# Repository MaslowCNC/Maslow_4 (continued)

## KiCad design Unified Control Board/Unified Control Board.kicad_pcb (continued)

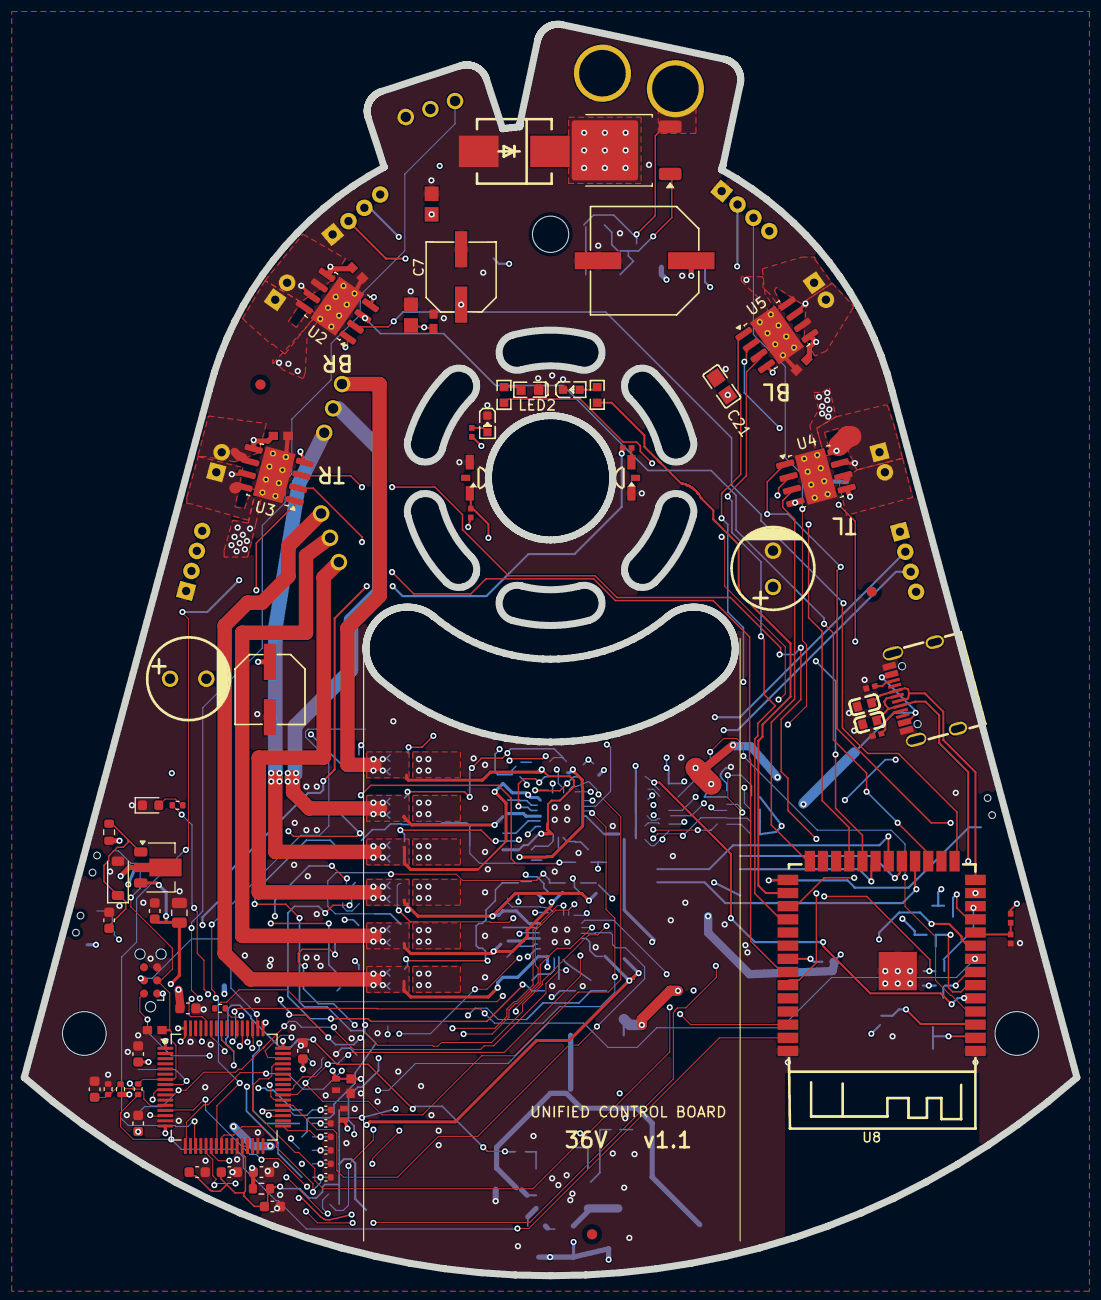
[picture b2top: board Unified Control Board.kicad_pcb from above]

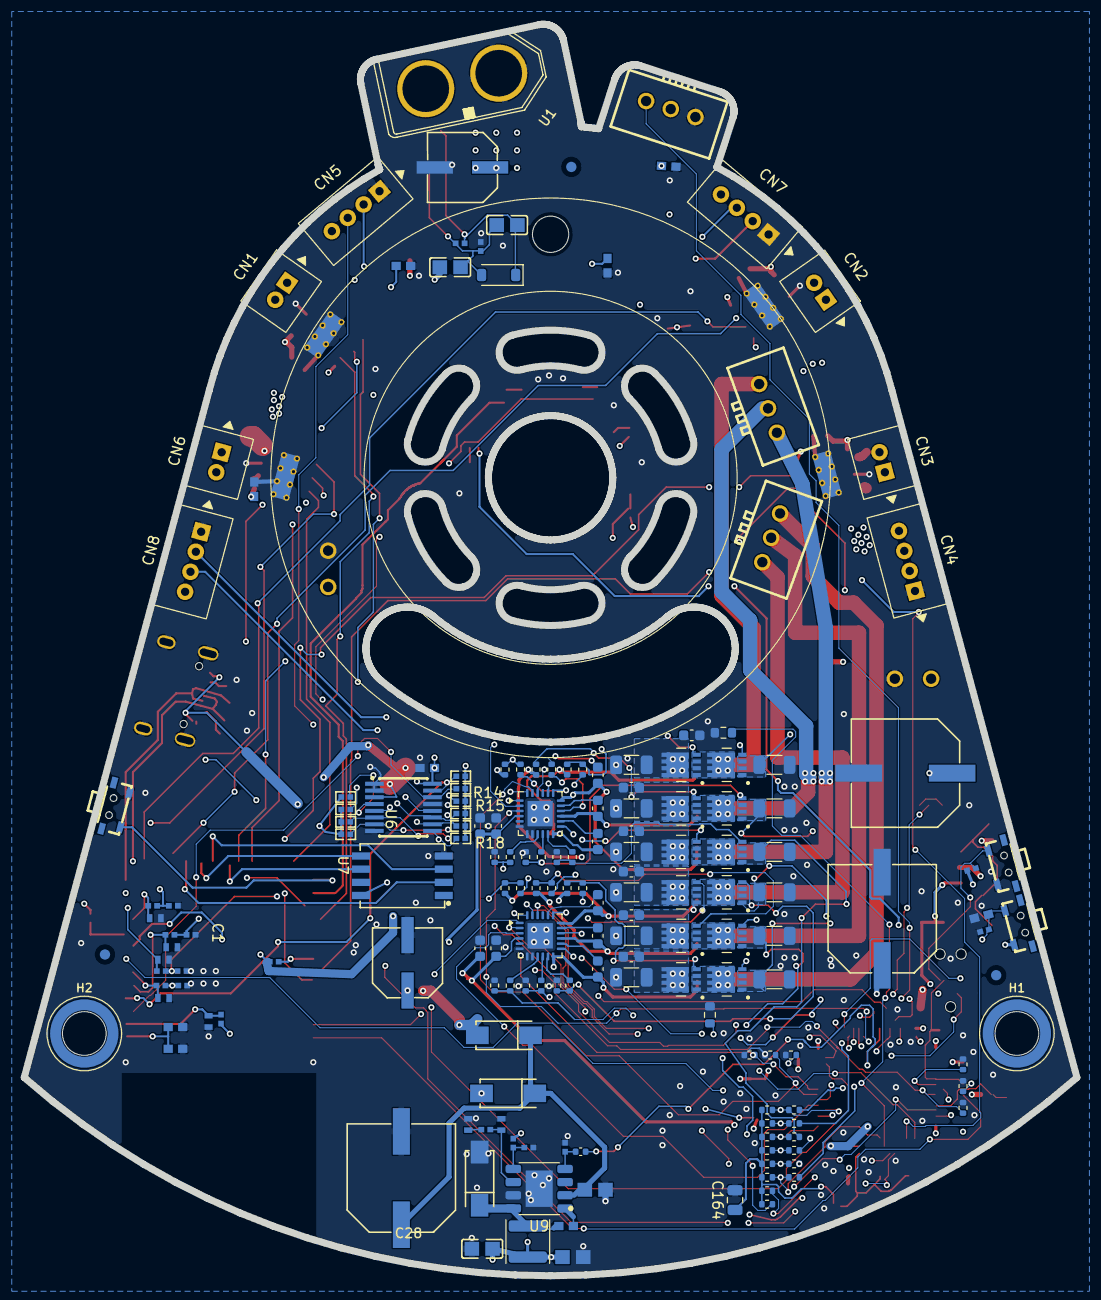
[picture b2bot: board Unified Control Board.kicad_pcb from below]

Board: 4 copper layers, 101.6 x 120.8 mm, 245 parts (172 on the bottom side), 145 nets.

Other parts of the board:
FID1, FID2, FID3, FID4, FID5, FID6: Fiducial; Fiducial_1mm_Mask2mm

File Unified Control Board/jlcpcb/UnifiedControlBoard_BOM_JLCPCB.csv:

"Comment","Designator","Footprint","LCSC Part #","Quantity"
"22uF","C1,C7,C10,C18","CAP-SMD_BD6.3-L6.6-W6.6-LS7.3-FD","C267472","4"
"100nF/100V","C5,C9,C16,C112,C113,C114,C132,C133,C134,C160,C161,C162,C163","C0603","C15725","13"
"1uF","C8,C11,C19,C20,C26,C40,C44","C0402","C52923","7"
"22uF","C21,C33,C56,C63,C164","C0805","C45783","5"
"100nF/50V","C22,C31,C34,C36,C42,C49,C54,C61,C101,C102,C103,C105,C121,C122,C123,C125,C140,C141,C142,C143,C146,C147,C150,C152,C153","C_0603_1608Metric","C14663","25"
"10uF/25V","C23,C72,C151","C0805","C15850","3"
"22pF","C24,C25","C0603","C105620","2"
"330uF/50V","C27,C74,C75","CAP-SMD_BD10.0-L10.3-W10.3-LS10.9-FD","C178596","3"
"220uF/50V","C28","CAP-SMD_BD10.0-L10.3-W10.3-LS10.9-FD","C116211","1"
"12nF","C29","C0402","C576739","1"
"82pF","C30","C0402","C107011","1"
"10uF","C32","C0805","C440198","1"
"100uF/50V","C39,C60","CAP-TH_BD8.0-P3.50-D0.6-FD","C88728","2"
"220nF/100V","C73","C0805","C513710","1"
"10uF/25V","C104,C124","C_0603_1608Metric","C91606","2"
"100pF","C106,C107,C108,C126,C127,C128","C_0402_1005Metric","C1546","6"
"1uF/100V","C109,C110,C111,C129,C130,C131","C_1206_3216Metric","C13832","6"
"4.7uF","C144","C_0603_1608Metric","C19666","1"
"1uF/50V","C145","C_0603_1608Metric","C15849","1"
"10pF","C165","C_0402_1005Metric","C32949","1"
"IR12-21C/TR8","CGQ1","LED-SMD_IR12-21C-TR8","C53672","1"
"B02B-PASK(LF)(SN)","CN1,CN2,CN3,CN6","CONN-TH_B02B-PASK","C158050","4"
"B04B-PASK(LF)(SN)","CN4,CN5,CN7,CN8","CONN-TH_B04B-PASK","C265078","4"
"B3B-XH-2(LF)(SN)","CN9,CN10,CN11","CONN-TH_B3B-XH-2-LF-SN","C158003","3"
"RB050L-60TE25","D1,D2,D5","SMA_L4.2-W2.6-LS5.3-RD","C209642","3"
"SMCJ36A","D3","SMC_L7.1-W6.2-LS8.1-R-RD","C151282","1"
"BZT52C15","D6","D_SOD-123","C173427","1"
"BZT52C13","D10","D_SOD-123","C173428","1"
"SMTSOM330BTR","H1,H2","SMTSO-M3_SMD-Ring_Hole4.22","C5221843","2"
"PT12-21C/TR8","IR1","SENSOR-SMD_L3.0-W2.0-RD","C53674","1"
"4.7uH","L1","L_APV_ANR4030","C167874","1"
"LED-0603_R","LED1","LED0603_RED","C2286","1"
"FC-DA1608BK-470H10","LED2","LED0603-RD","C84266","1"
"green","LED3,LED4","LED0603-RD-YELLOW","C2289","2"
"ME50P06-G","Q1","TO-252-2","C165230","1"
"AON7264E","Q10,Q11,Q12,Q13,Q14,Q15,Q20,Q21,Q22,Q23,Q24,Q25","AOS_DFN-8-1EP_3x3mm_P0.65mm","C431191","12"
"BCX56-16","Q30","SOT-89-3","C123402","1"
"680Ω","R1,R11,R12,R21","R0402","C25130","4"
"120Ω","R2,R3","R0603","C22787","2"
"2.2kΩ","R4","R0402","C25879","1"
"1kΩ","R5,R7,R14,R15,R16,R17,R18,R22,R23,R24,R116,R117,R118,R146,R147,R148,R175,R176,R177","R0402","C11702","19"
"5.1kΩ","R8,R13","R0402","C25905","2"
"10kΩ","R9,R10,R19,R20,R25,R26,R28,R38,R39,R45,R107,R108,R109,R110,R111,R112,R137,R138,R139,R140,R141,R142,R173,R174","R_0402_1005Metric","C25744","24"
"62kΩ","R27","R0402","C37825","1"
"20kΩ","R29","R0402","C25765","1"
"200kΩ","R30","R0402","C25764","1"
"7.5kΩ","R31","R0402","C25918","1"
"100Ω","R44","R0402","C25076","1"
"330Ω","R58","R0402","C25104","1"
"47kΩ","R59","R0402","C25792","1"
"100kΩ","R60,R171","R0402","C25741","2"
"15","R101,R102,R103,R104,R105,R106,R131,R132,R133,R134,R135,R136","R_0402_1005Metric","C25083","12"
"5m","R113,R114,R115,R143,R144,R145","R_1206_3216Metric","C201272","6"
"31.6k","R119,R120,R121,R149,R150,R151","R_0402_1005Metric","C11463","6"
"4.7k","R160,R161,R162,R163,R164,R165","R_0402_1005Metric","C25900","6"
"10k","R170","R_0603_1608Metric","C25804","1"
"6.8k","R172","R_0402_1005Metric","C25917","1"
"4.7","R178","R_0603_1608Metric","C144651","1"
"10k NTC","RT1,RT2","R_0603_1608Metric","C13564","2"
"TSA002A3512A02","SW1,SW2,SW3","SW-SMD_BZCN_TSA002A35XXX","C2888932","3"
"XT60PB-M.G.Y","U1","CONN-TH_XT60PB-M","C19268037","1"
"DRV8251ADDAR","U2,U3,U4,U5","SOIC-8-1EP_DDA0008B_ThermalVias_0.3mm","C5218844","4"
"TCA9546A","U6","SOP-16_L5.0-W4.4-P0.65-LS6.4-BL","C201653","1"
"ZDSD01GLGEAG","U7","LGA-8_L6.0-W8.0-P1.27-BL","C2830323","1"
"ESP32-S3-WROOM-1","U8","ESP32-S3-WROOM-1","C2913204","1"
"TPS54360BDDAR","U9","AP64350SP_SO-8-EP","C524806","1"
"STM32G474RBT3","U20","LQFP-64_10x10mm_P0.5mm","C1235414","1"
"DRV8300DRGE","U21,U22","VQFN-24-1EP_4x4mm_P0.5mm_EP2.45x2.45mm","C3655801","2"
"KH-TYPE-C-16P","USB1","USB-C-SMD_KH-TYPE-C-16P","C709357","1"

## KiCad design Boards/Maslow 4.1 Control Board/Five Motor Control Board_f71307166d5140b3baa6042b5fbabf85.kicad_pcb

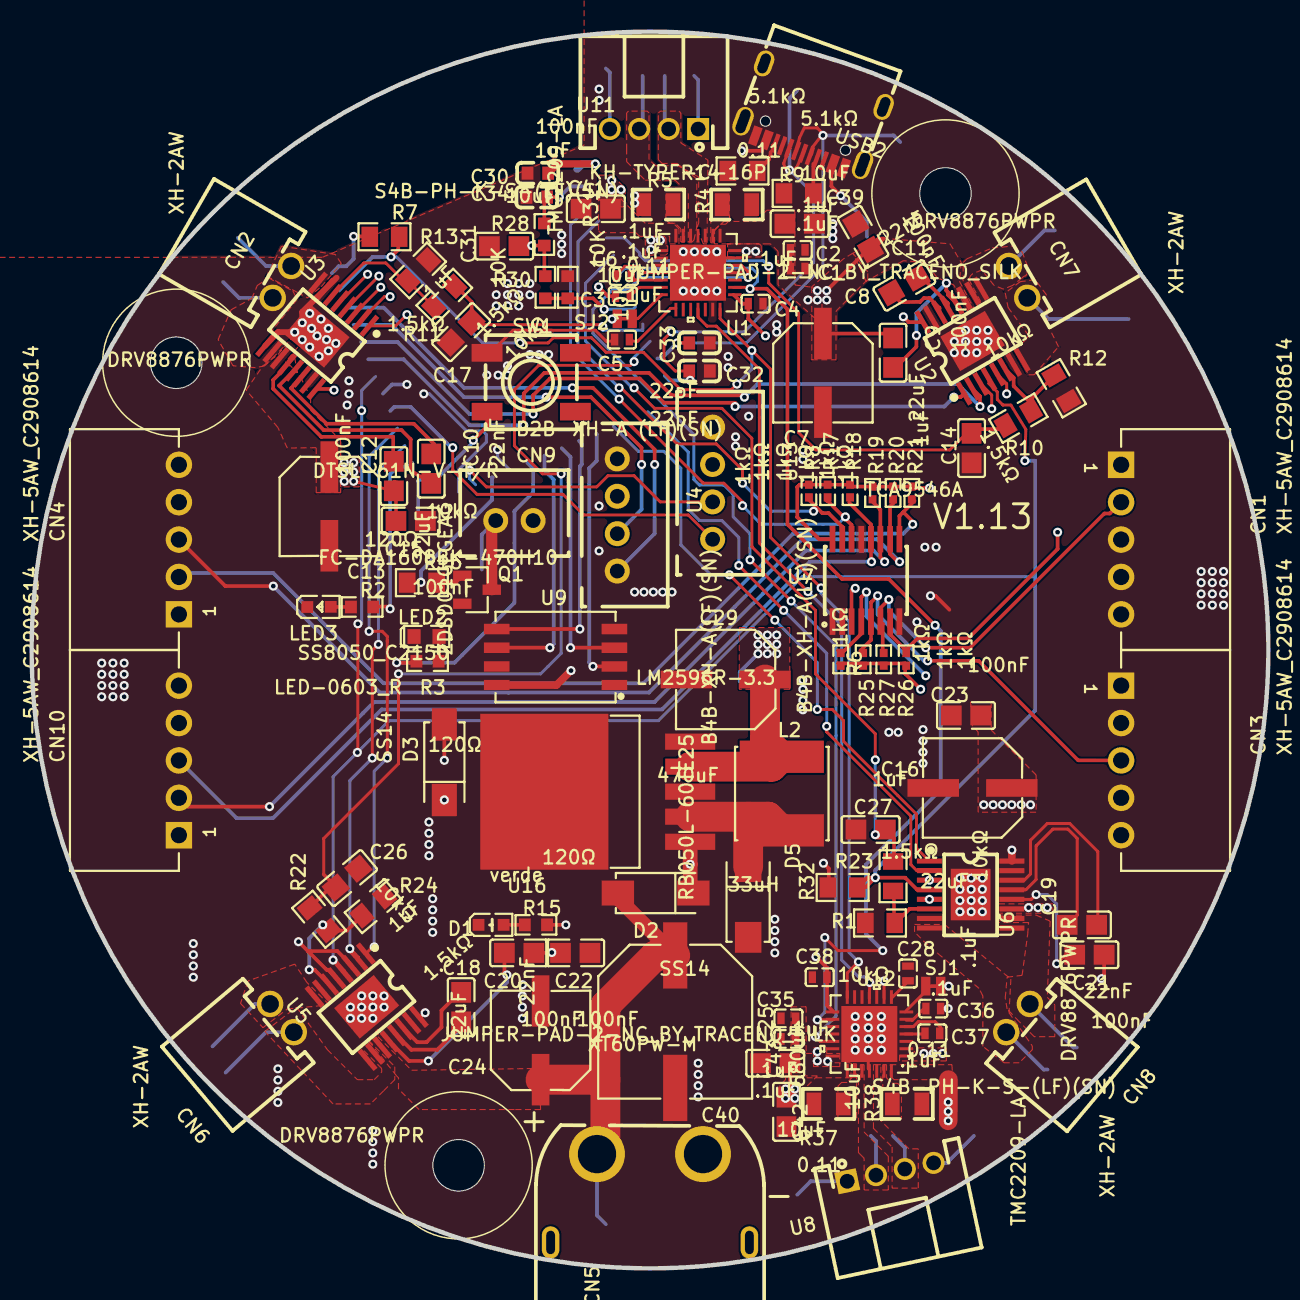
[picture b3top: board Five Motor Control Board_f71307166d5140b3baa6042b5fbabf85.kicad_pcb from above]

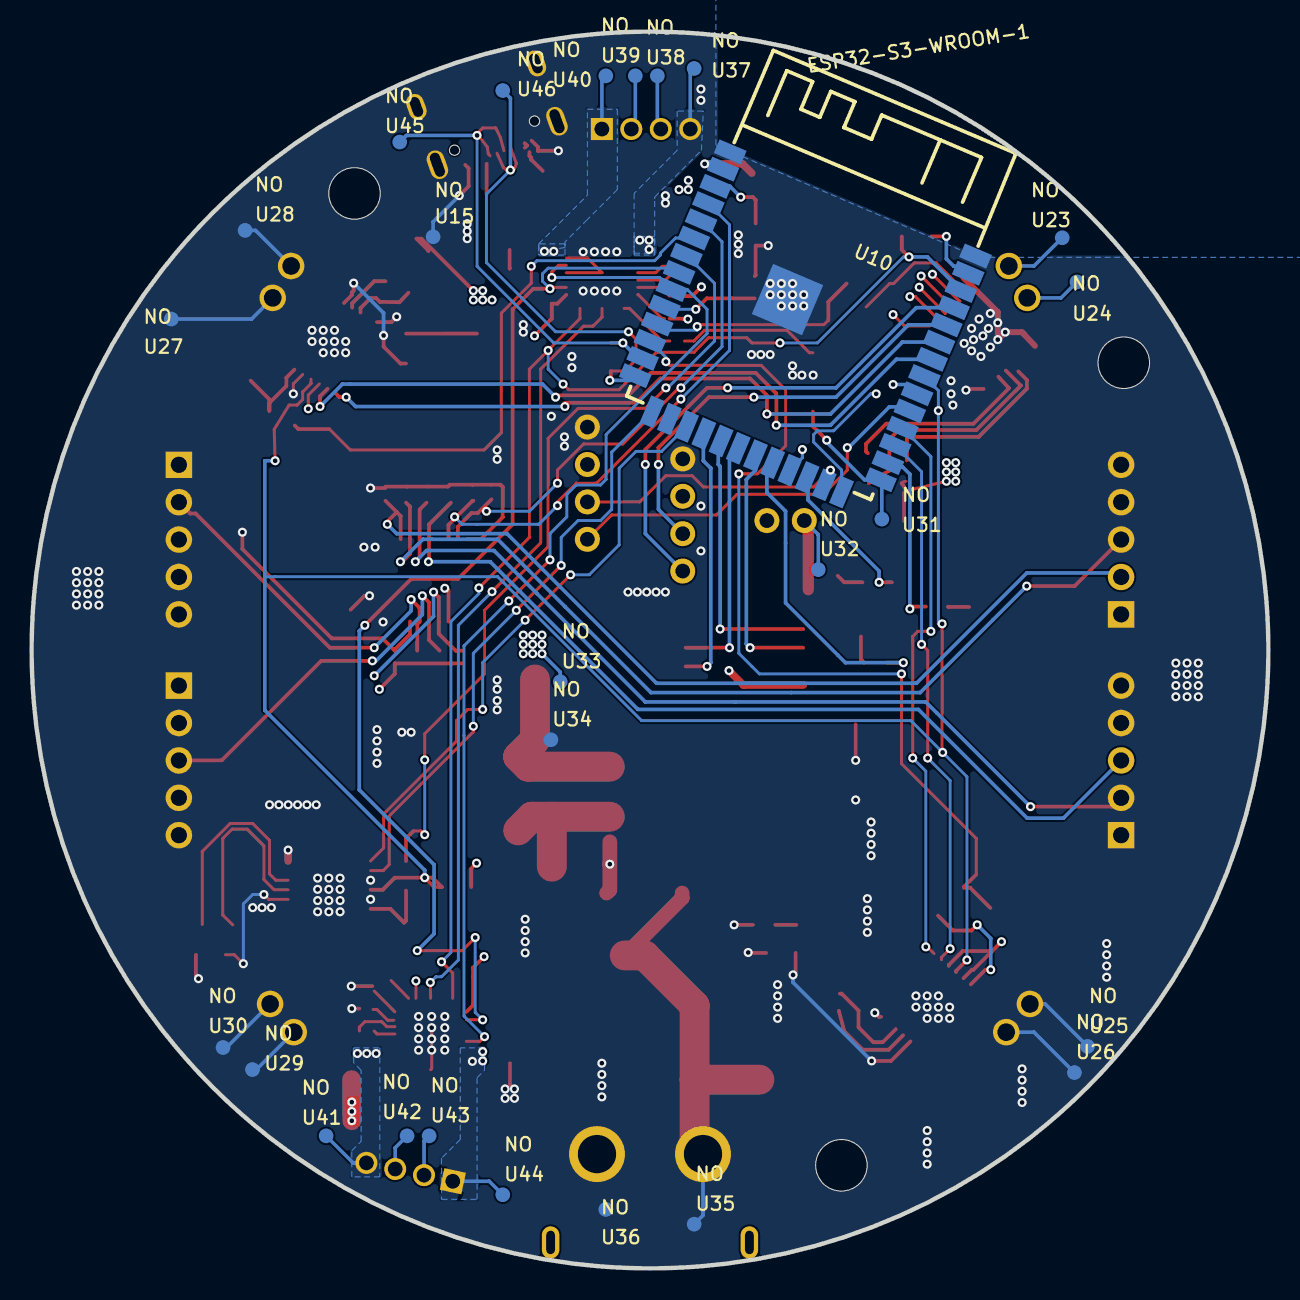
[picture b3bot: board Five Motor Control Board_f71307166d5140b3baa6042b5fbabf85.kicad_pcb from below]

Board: 4 copper layers, 84.0 x 84.0 mm, 140 parts (26 on the bottom side), 103 nets.

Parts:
C1, C2, C3, C4, C5, C6, C25, C28, C35, C36, C37, C38: .1uF; C0402
C7, C13, C16, C24: 22uF; CAP-SMD_BD6.3-L6.6-W6.6-LS7.3-FD
C8, C10, C18, C19: 22nF; C0805
C9, C11, C12, C15, C20, C21, C22, C23: 100nF; C0805
C14, C17, C26, C27: 1uF; C0805
C29: 470uF; CAP-SMD_BD6.3-L6.6-W6.6-LS7.6-RD
C30: 100nF; C0603
C31, C39, C41, C42, C43: 10uF; C0805
C32, C33: 22pF; C0603
C34: 1uF; C0603
C40: 680uF; CAP-SMD_BD10.0-L10.3-W10.3-LS10.9-FD
CN1, CN3, CN4, CN10: XH-5AW_C2908614; CONN-TH_5P-P2.54_XH-5AW_C2908614
CN2, CN6, CN7, CN8: XH-2AW; CONN-TH_2P-P2.50_XH-2AW
CN5: XT60PW-M; CONN-TH_XT60PW-M
CN9: B2B-XH-A (LF)(SN); CONN-TH_B2B-XH-A-LF-SN
D1: verde; LED0603-R-RD
D2, D3: SS14; SMA_L4.2-W2.6-LS5.3-RD
D5: RB050L-60TE25; SMA_L4.3-W2.7-LS5.1-RD
Hole_gge29897: Hole_gge29897
Hole_gge29907: Hole_gge29907
Hole_gge29912: Hole_gge29912
L2: 33uH; IND-SMD_L6.0-W6.0
LED2: LED-0603_R; LED0603_RED
LED3: FC-DA1608BK-470H10; LED0603-RD
Q1: SS8050_C2150; SOT-23-3_L2.9-W1.3-P1.90-LS2.4-BR
R1, R7, R12, R13, R24: 1.5kΩ; R0805
R2, R3, R15: 120Ω; R0603
R4, R5, R37, R38: 0.11; R0805
R6, R8, R17, R18, R19, R20, R21, R25, R26, R27: 1kΩ; R0402
R9, R14: 5.1kΩ; R0805
R10, R11, R16, R22, R23, R32: 10kΩ; R0805
R28, R30, R31: 10K; R0603
SJ1, SJ2: JUMPER-PAD-2-NC_BY_TRACENO_SILK; PAD-JUMPER-2-NC_BY_TRACE_NO_SILK
SW1: DTSL-61N-V-T/R; SW-SMD_4P-L6.2-W6.4-P4.00-LS7.2
U1, U12: TMC2209-LA
U2, U3, U5, U6: DRV8876PWPR; HTSSOP-16_L5.0-W4.4-P0.65-LS6.4-BL-EP
U4, U13: B4B-XH-A(LF)(SN); CONN-TH_B4B-XH-A-LF-SN
U7: TCA9546A; SOP-16_L5.0-W4.4-P0.65-LS6.4-BL
U8, U11: S4B-PH-K-S-(LF)(SN); CONN-TH_4P-P2.00_S4B-PH-K-S-LF-SN
U9: ZDSD01GLGEAG; LGA-8_L6.0-W8.0-P1.27-BL
U10: ESP32-S3-WROOM-1
U15, U23, U24, U25, U26, U27, U28, U29, U30, U31, U32, U33, U34, U35, U36, U37, U38, U39, U40, U41, U42, U43, U44, U45, U46: NO; 1-POINT_TEST-POINT
U16: LM2596R-3.3; TO-263-5_L10.2-W8.6-P1.70-LS14.4-TL
USB2: KH-TYPE-C-16P; USB-C-SMD_KH-TYPE-C-16P

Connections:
3V3: C4.1, C29.1, C30.2, C31.2, C38.1, CN1.1, CN3.1, CN4.1, CN10.1, L2.2, R6.2, R8.2, R15.2, R17.2, R18.2, R19.2, R20.2, R21.2, R25.2, R26.1, R27.2, R28.2, R30.2, R32.2, SJ1.1, SJ2.1, U1.15, U2.3, U2.5, U2.16, U3.3, U3.5, U3.16, U4.2, U5.3, U5.5, U5.16, U6.3, U6.5, U6.16, U7.3, U7.16, U9.8, U10.2, U12.9, U12.15, U13.2, U16.4, U33.1
A1+: U8.2, U12.24, U43.1
A1-: U8.1, U12.21, U44.1
A2+: U1.24, U11.2, U39.1
A2-: U1.21, U11.1, U40.1
ADCBL: C26.2, R22.1, U10.12
ADCBR: C27.2, R23.1, U10.7
ADCTL: C17.2, R11.1, U10.11
ADCTR: C14.2, R10.1, U10.6
AUX1: U10.25, U13.3
AUX2: U10.31, U13.4
AXISHEALTHLED: R3.2, U10.22
B1+: U8.3, U12.26, U42.1
B1-: U8.4, U12.1, U41.1
B2+: U1.26, U11.3, U38.1
B2-: U1.1, U11.4, U37.1
BLIN1: U5.1, U10.30
BLIN2: U5.2, U10.29
BLOUT1: CN6.2, U5.8, U25.1
BLOUT2: CN6.1, U5.10, U26.1
BOARDVERSION: R30.1, R31.2, U10.10
BOOT: SW1.2, U10.27, U31.1
BRIN1: U6.1, U10.17
BRIN2: U6.2, U10.15
BROUT1: CN8.2, U6.8, U29.1
BROUT2: CN8.1, U6.10, U30.1
C3_2: C3.2, U1.6
CLKV: U9.3, U10.20
COOLINGFAN: R16.1, U10.24
D1_1: D1.1, R15.1
DIAG: U1.11, U12.11
FAULT: R32.1, U2.4, U3.4, U5.4, U6.4, U10.33
GND: C1.2, C2.2, C4.2, C5.1, C7.2, C11.1, C13.2, C14.1, C15.1, C16.2, C17.1, C22.1, C23.1, C24.2, C25.2, C26.1, C27.1, C28.1, C29.2, C30.1, C31.1, C32.1, C33.1, C34.1, C35.2, C38.2, C39.2, C40.2, C41.2, C42.2, C43.2, CN1.4, CN1.5, CN3.4, CN3.5, CN4.4, CN4.5, CN5.1, CN10.4, CN10.5, D1.2, D5.2, LED2.2, LED3.1, Q1.2, R1.1, R4.2, R5.2, R9.1, R12.1, R13.1, R14.1, R24.1, R31.1, R37.2, R38.2, SW1.4, U1.2, U1.3, U1.13, U1.18, U1.20, U1.25, U1.29, U2.7, U2.9, U2.15, U2.17, U3.7, U3.9, U3.15, U3.17, U4.1, U5.7, U5.9, U5.15, U5.17, U6.7, U6.9, U6.15, U6.17, U7.1, U7.2, U7.8, U7.13, U9.4, U10.1, U10.40, U10.41, U12.2, U12.3, U12.13, U12.18, U12.20, U12.25, U12.29, U13.1, U16.3, U16.5, U34.1, U36.1, USB2.1, USB2.2, USB2.3, USB2.4, USB2.A1, USB2.A12, USB2.B1, USB2.B12
L2_1: D5.1, L2.1, U16.2
LED2_1: LED2.1, R3.1
LED3_2: LED3.2, R2.1
MCU_RST: C34.2, R28.1, U10.3
MISOV: U9.6, U10.21
MOSIV: U9.5, U10.19
MZDIRECTION: U1.19, U10.9, U12.19
MZSTEP: U1.16, U10.8, U12.16
Q1_1: Q1.1, R16.2
Q1_3: CN9.2, Q1.3, U32.1
R4_1: R4.1, U1.23
R5_1: R5.1, U1.27
SCL: R17.1, U7.14, U10.4
SCL0: CN3.3, R25.1, U7.5
SCL1: CN1.3, R26.2, U7.7
SCL2: CN4.3, R20.1, U7.10
SCL3: CN10.3, R18.1, U7.12
SDA: R8.1, U7.15, U10.5
SDA0: CN3.2, R6.1, U7.4
SDA1: CN1.2, R27.1, U7.6
SDA2: CN4.2, R21.1, U7.9
SDA3: CN10.2, R19.1, U7.11
SD_CS: U9.2, U10.18
SERIALRX: U4.3, U10.36
SERIALTX: U4.4, U10.37
TLIN1: U3.1, U10.26
TLIN2: U3.2, U10.23
TLOUT1: CN2.2, U3.8, U23.1
TLOUT2: CN2.1, U3.10, U24.1
TRIN1: U2.1, U10.35
TRIN2: U2.2, U10.34
TRINAMICRX: R7.1, U1.14, U10.38, U12.14
TRINAMICTX: R7.2, U10.39
TROUT1: CN7.2, U2.8, U27.1
TROUT2: CN7.1, U2.10, U28.1
U1_4: C6.1, U1.4
U1_5: C6.2, U1.5
U1_7: SJ2.2, U1.7
U1_8: C5.2, U1.8
U2_6: R10.2, R12.2, U2.6
U2_12: C9.2, U2.12
U2_13: C8.2, U2.13
U2_14: C8.1, U2.14
U3_6: R11.2, R13.2, U3.6
U3_12: C12.2, U3.12
U3_13: C10.2, U3.13
U3_14: C10.1, U3.14
U5_6: R22.2, R24.2, U5.6
U5_12: C20.2, U5.12
U5_13: C18.2, U5.13
U5_14: C18.1, U5.14
U6_6: R1.2, R23.2, U6.6
U6_12: C21.2, U6.12
U6_13: C19.2, U6.13
U6_14: C19.1, U6.14
U12_4: C37.1, U12.4
U12_5: C37.2, U12.5
U12_6: C36.2, U12.6
U12_7: SJ1.2, U12.7
U12_8: C28.2, U12.8
U12_23: R37.1, U12.23
U12_27: R38.1, U12.27
U16_1: D2.1, D3.1, U16.1
USB2_A5: R9.2, USB2.A5
USB2_B5: R14.2, USB2.B5
USB5V: D3.2, U15.1, USB2.A4, USB2.A9, USB2.B4, USB2.B9
USBD+: C32.2, U10.14, U46.1, USB2.A6, USB2.B6
USBD-: C33.2, U10.13, U45.1, USB2.A7, USB2.B7
VCC: C1.1, C2.1, C3.1, C7.1, C9.1, C11.2, C12.1, C13.1, C15.2, C16.1, C20.1, C21.1, C22.2, C23.2, C24.1, C25.1, C35.1, C36.1, C39.1, C40.1, C41.1, C42.1, C43.1, CN5.2, CN9.1, D2.2, U1.22, U1.28, U2.11, U3.11, U5.11, U6.11, U12.22, U12.28, U35.1
WIFILED: R2.2, U10.28

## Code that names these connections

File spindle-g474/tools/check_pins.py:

#!/usr/bin/env python3
"""Check the G474 firmware's pin map (src/board.h) against the board's KiCad netlist.

Exports the netlist of "Unified Control Board/Unified Control Board.kicad_sch" with kicad-cli and
checks every MCU pin the firmware uses, plus the parts around it whose values the firmware
assumes (shunts, sense resistors, VBUS divider, NTCs, BoardVersion divider, XY<->G474 wiring).

    python3 spindle-g474/tools/check_pins.py [--kicad-cli PATH]

Exit status 0 = everything matches.
"""
import argparse, os, shutil, subprocess, sys, tempfile
import xml.etree.ElementTree as ET

HERE = os.path.dirname(os.path.abspath(__file__))
SCH = os.path.join(HERE, "..", "..", "Unified Control Board", "Unified Control Board.kicad_sch")

# U20 (STM32G474RBT3, LQFP64) pin -> (pin name, net) the firmware expects.
MCU = {
    "8": ("PC0", "INHA1"), "9": ("PC1", "INHB1"), "10": ("PC2", "INHC1"),
    "45": ("PA11", "INLA1"), "46": ("PA12", "INLB1"), "37": ("PB15", "INLC1"),
    "38": ("PC6", "INHA2"), "39": ("PC7", "INHB2"), "40": ("PC8", "INHC2"),
    "52": ("PC10", "INLA2"), "53": ("PC11", "INLB2"), "54": ("PC12", "INLC2"),
    "13": ("PA1", "ISA1"), "21": ("PA7", "ISB1"), "24": ("PB0", "ISC1"),
    "33": ("PB11", "ISA2"), "36": ("PB14", "ISB2"), "35": ("PB13", "ISC2"),
    "12": ("PA0", "VBUS_SENSE"), "22": ("PC4", "TEMP1"), "23": ("PC5", "TEMP2"),
    "14": ("PA2", "BoardCOM1"), "17": ("PA3", "BoardCOM2"),
    "19": ("PA5", "BEAMBREAK"), "60": ("PB7", "DETECTORLED"), "51": ("PA15", "SPINDLE_LED"),
    "59": ("PB6", "VAC_CONTROL"), "49": ("PA13", "SWDIO"), "50": ("PA14", "SWCLK"),
    "7": ("PG10", "SPINDLE_NRST"), "61": ("PB8", "SPINDLE_BOOT0"),
    "28": ("VREF+", "3V3A"), "29": ("VDDA", "3V3A"),
}

# (net, ref, pin) connections the firmware relies on.
LINKS = [
    # gate driver inputs: U21 = motor 1, U22 = motor 2 (DRV8300: INLA/B/C = 1/2/3, INHA/B/C = 22/23/24)
    ("INLA1", "U21", "1"), ("INLB1", "U21", "2"), ("INLC1", "U21", "3"),
    ("INHA1", "U21", "22"), ("INHB1", "U21", "23"), ("INHC1", "U21", "24"),
    ("INLA2", "U22", "1"), ("INLB2", "U22", "2"), ("INLC2", "U22", "3"),
    ("INHA2", "U22", "22"), ("INHB2", "U22", "23"), ("INHC2", "U22", "24"),
    # XY ESP32-S3 (U8): IO15 (pin 8) = BoardCOM2 -> G474 RX, IO16 (pin 9) = BoardCOM1 <- G474 TX
    ("BoardCOM2", "U8", "8"), ("BoardCOM1", "U8", "9"),
    # XY control of the G474's reset and boot pins through 1k: IO1 (pin 39), IO2 (pin 38)
    ("SPINDLE_RST_X", "U8", "39"), ("SPINDLE_BOOT_X", "U8", "38"),
    ("BoardVersion", "U8", "10"),
    # each sense input reads the shunt under the low-side FET of the phase the firmware assumes:
    # IS<x><m> <- 1k <- S<x><m> = source of the low-side FET whose drain (pin 5) is PH<x><m>
    ("SA1", "R116", "1"), ("SA1", "Q11", "1"), ("PHA1", "Q11", "5"),
    ("SB1", "R117", "1"), ("SB1", "Q13", "1"), ("PHB1", "Q13", "5"),
    ("SC1", "R118", "1"), ("SC1", "Q15", "1"), ("PHC1", "Q15", "5"),
    ("SA2", "R146", "1"), ("SA2", "Q21", "1"), ("PHA2", "Q21", "5"),
    ("SB2", "R147", "1"), ("SB2", "Q23", "1"), ("PHB2", "Q23", "5"),
    ("SC2", "R148", "1"), ("SC2", "Q25", "1"), ("PHC2", "Q25", "5"),
    ("ISB1", "R117", "2"), ("ISC1", "R118", "2"), ("ISB2", "R147", "2"), ("ISC2", "R148", "2"),
]

# ref -> value the firmware's constants assume
VALUES = {
    "R113": "5m", "R114": "5m", "R115": "5m",   # shunts (SHUNT_OHMS)
    "R143": "5m", "R144": "5m", "R145": "5m",
    "R171": "100k", "R172": "6.8k",           # VBUS divider (board.h VBUS_DIVIDER)
    "R173": "10k", "R174": "10k",             # NTC pull-ups
    "RT1": "10k NTC", "RT2": "10k NTC",       # NCP18XH103F03RB, B 3380
    "R116": "1k", "R119": "31.6k",            # sense bias network (SENSE_DIVIDER), motor 1 phase A
    "R146": "1k", "R149": "31.6k",
    "R26": "10kΩ", "R4": "2.2kΩ",             # BoardVersion 10k / 2.2k -> ~0.60 V = Unified36V band
    "R160": "4.7k", "R163": "4.7k",           # high-side input pull-downs
}


def main():
    ap = argparse.ArgumentParser()
    ap.add_argument("--kicad-cli", default=shutil.which("kicad-cli") or
                    "/Applications/KiCad/KiCad.app/Contents/MacOS/kicad-cli")
    args = ap.parse_args()
    with tempfile.TemporaryDirectory() as tmp:
        net = os.path.join(tmp, "ucb.xml")
        subprocess.run([args.kicad_cli, "sch", "export", "netlist", "--format", "kicadxml", "-o", net, SCH],
                       check=True, stdout=subprocess.DEVNULL, stderr=subprocess.DEVNULL)
        root = ET.parse(net).getroot()

    vals = {c.get("ref"): c.findtext("value") for c in root.iter("comp")}
    pinnet, pinfn = {}, {}
    for n in root.iter("net"):
        for node in n.iter("node"):
            pinnet[(node.get("ref"), node.get("pin"))] = n.get("name")
            pinfn[(node.get("ref"), node.get("pin"))] = node.get("pinfunction") or ""

    bad = 0
    mcu = [r for r, v in vals.items() if v and "G474" in v]
    if mcu != ["U20"]:
        print(f"FAIL  expected one STM32G474 as U20, found {mcu}")
        bad += 1
    for pin, (name, want) in MCU.items():
        got, fn = pinnet.get(("U20", pin)), pinfn.get(("U20", pin), "")
        ok = got == want and fn.split("_")[0] == name
        bad += not ok
        print(f"{'ok  ' if ok else 'FAIL'}  U20.{pin:<3} {name:<6} {want:<15} netlist: {fn} {got}")
    for want, ref, pin in LINKS:
        got = pinnet.get((ref, pin))
        ok = got == want
        bad += not ok
        print(f"{'ok  ' if ok else 'FAIL'}  {ref}.{pin:<4} {want:<15} netlist: {got}")
    for ref, want in VALUES.items():
        ok = vals.get(ref) == want
        bad += not ok
        print(f"{'ok  ' if ok else 'FAIL'}  {ref:<6} = {want:<10} netlist: {vals.get(ref)}")
    print(f"\n{bad} mismatch(es)")
    return 1 if bad else 0


if __name__ == "__main__":
    sys.exit(main())

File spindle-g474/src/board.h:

#pragma once
// Pin map and fixed hardware facts of the 36 V Unified Control Board's spindle drive (sheet
// "Spindle Drive", U20 = STM32G474RBT3).  Every pin below was checked against the KiCad netlist
// exported from branch 36V-G474-spindle (kicad-cli sch export netlist, Unified Control Board.kicad_sch)
// and the alternate functions against the Arduino core's PeripheralPins.c / ST's HAL headers.
// BRINGUP.md lists the check.
//
//  Net            G474 pin       Use
//  INHA1/B1/C1    PC0/PC1/PC2    TIM1_CH1..3   (AF2)  motor 1 high-side inputs, U21 DRV8300 (4.7k pull-downs)
//  INLA1/B1       PA11/PA12      TIM1_CH1N/2N  (AF6)  motor 1 low-side inputs
//  INLC1          PB15           TIM1_CH3N     (AF4)
//  INHA2/B2/C2    PC6/PC7/PC8    TIM8_CH1..3   (AF4)  motor 2 high-side inputs, U22 DRV8300
//  INLA2/B2/C2    PC10/PC11/PC12 TIM8_CH1N..3N (AF4)  motor 2 low-side inputs
//  ISA1/B1/C1     PA1/PA7/PB0    OPAMP1/2/3 VINP0, COMP1/2/4 INP (IO1)   5 mOhm low-side shunts, motor 1
//  ISA2           PB11           OPAMP4 VINP2, COMP6 INP (IO1)           motor 2 phase A
//  ISB2           PB14           OPAMP5 VINP0, COMP7 INP (IO1)           motor 2 phase B
//  ISC2           PB13           OPAMP6 VINP2, COMP5 INP (IO1)           motor 2 phase C
//  VBUS_SENSE     PA0            ADC12_IN1      100k / 6.8k divider (52 V full scale)
//  TEMP1/TEMP2    PC4/PC5        ADC2_IN5/IN11  10k pull-up from 3V3A to an NCP18XH103 NTC (B 3380)
//  BoardCOM1      PA2            USART2_TX (AF7) -> XY ESP32-S3 IO16 (its RX)
//  BoardCOM2      PA3            USART2_RX (AF7) <- XY ESP32-S3 IO15 (its TX)
//  BEAMBREAK      PA5            input, phototransistor with a 10k pull-up: HIGH = beam interrupted
//  DETECTORLED    PB7            output, IR emitter through 100R (on = beam active)
//  SPINDLE_LED    PA15           output, green LED4 through 1k
//  VAC_CONTROL    PB6            TIM4_CH1 (AF2) -> CN10 pin 1 (pin 2 is VCC, 36 V)
//  SWDIO/SWCLK    PA13/PA14      TC2030 J1
//  SPINDLE_NRST   PG10/NRST      10k up, 100 nF, SW2, and the XY board's IO1 through 1k
//  SPINDLE_BOOT0  PB8/BOOT0      10k down, SW3 up, and the XY board's IO2 through 1k
//
// The DRV8300 has no fault output and no enable pin: the timers' MOE bit is the only off switch,
// and the six comparators trip the timers' break inputs in hardware.

#include <Arduino.h>

// ---- Shunt sense chain (Spindle Drive sheet note) ----
// VINP = 3V3A * 1k/32.6k + 0.969 * I * 5 mOhm; the OPAMP's PGA multiplies by 16 into the ADC.
// 1.62 V at 0 A, 77.5 mV/A, about +-21 A of ADC range.  The zero is measured at boot.
constexpr float SHUNT_OHMS          = 0.005f;
constexpr float SENSE_DIVIDER       = 31.6f / 32.6f;   // the 1k / 31.6k bias network's attenuation
constexpr float PGA_GAIN            = 16.0f;
constexpr float ADC_VREF            = 3.3f;            // VREF+ = 3V3A
constexpr float ADC_FULL_SCALE      = 4096.0f;
constexpr float SENSE_V_PER_A       = SHUNT_OHMS * SENSE_DIVIDER * PGA_GAIN;          // 0.0775 V/A
constexpr float SENSE_A_PER_LSB     = ADC_VREF / ADC_FULL_SCALE / SENSE_V_PER_A;      // ~0.0104 A
// A positive phase current (out of the bridge into the motor) flows up through the low-side
// shunt while the low side conducts, so the shunt node goes NEGATIVE: the reading falls.
// Verify with "#ALIGN" at bring-up (BRINGUP.md step 4).
constexpr float SENSE_SIGN          = -1.0f;
// The comparators see VINP itself (before the PGA): 0.101 V at 0 A and 4.85 mV/A.
constexpr float VINP_ZERO_V         = ADC_VREF / 32.6f;
constexpr float VINP_V_PER_A        = SHUNT_OHMS * SENSE_DIVIDER;

// ---- Bus voltage divider: 100k over 6.8k ----
constexpr float VBUS_DIVIDER        = (100.0f + 6.8f) / 6.8f;   // 15.7: 3.3 V at the pin = 51.8 V

// ---- NTCs: 10k pull-up to 3V3A, NCP18XH103F03RB to GND ----
constexpr float NTC_R25             = 10000.0f;
constexpr float NTC_B               = 3380.0f;
constexpr float NTC_PULLUP          = 10000.0f;

// ---- PWM ----
constexpr uint32_t TIMER_CLOCK_HZ   = 170000000;
#ifdef PWM_FREQUENCY_OVERRIDE_HZ   // bring-up experiments, e.g. moving the 3V3 buck's alias (BRINGUP.md)
constexpr uint32_t PWM_FREQUENCY_HZ = PWM_FREQUENCY_OVERRIDE_HZ;
#else
constexpr uint32_t PWM_FREQUENCY_HZ = 20000;
#endif
// Centre-aligned: the counter goes 0 -> ARR -> 0 once per PWM period.
constexpr uint32_t PWM_ARR          = TIMER_CLOCK_HZ / (2 * PWM_FREQUENCY_HZ);   // 4250
constexpr float    PWM_PERIOD_S     = 1.0f / PWM_FREQUENCY_HZ;
// The ADC trigger (TIM1 OC4REF on TRGO2) is high while CNT > ARR - SAMPLE_LEAD_TICKS: it rises
// 118 ns before the peak and stays high 235 ns, several ADC clocks (23.5 ns at 42.5 MHz), so the
// ADCs cannot miss it.  The 0.29 us sampling window then sits about centred on the peak.
constexpr uint32_t SAMPLE_LEAD_TICKS = 20;
// The DRV8300 (DT pin open) adds its own 200 ns.  The timer's dead time is on top of it, so a
// timer whose outputs are ever driven straight to FETs elsewhere is never left without one.
constexpr uint32_t DEADTIME_NS      = 100;

// ---- U9 (TPS54360B 3V3 buck) sync clock: PB4 = TIM3_CH1 (AF2), through 10-22 pF into U9 RT/CLK ----
// v1.1 has C165 + net U9_SYNC; a v1.0 board needs the bodge in REVISIONS.md (PB4 is unconnected without it).
// 500 kHz = exactly 25 clocks per 20 kHz PWM period (8500 / 340 ticks), started from TIM1's update event at
// the peak, so the buck's switching keeps a fixed phase against the current samples.  Rank 1 of every ADC samples
// at about +15 ticks from the peak, ADC5's rank 2 (motor 2 phase B) about 120 ticks later.
// Phase sweeps on board 2 (v1.0 + bodge, BRINGUP.md "Board 2"), sd of the six channels:
//  - 36 V, logic load only: quiet (rms 10-11 counts, unsynchronised 120) for a rising edge 10-40 ticks after the
//    peak, worse from 5 and 45, a plateau of 30-40 at 110-240 and worse than unsynchronised at 280-320.  U9 runs in
//    discontinuous mode there (short on-time, then the inductor current reaches zero and the switch node rings),
//    so more than its two edges matter.
//  - USB power (U9 from 4.6 V, on-time ~1.35 us): quiet at 30 and 140-190.
// 30 is inside both.  Check it again under motor load (the 36 V rail moves, the logic load does not).
constexpr uint32_t SYNC_PERIOD_TICKS = 340;   // 500 kHz at 170 MHz
constexpr uint32_t SYNC_HIGH_TICKS   = 17;    // 100 ns high pulse
constexpr uint32_t SYNC_RISE_TICKS   = 30;    // rising edge, ticks after the PWM peak (0 .. 339)
// The clock must divide the PWM period exactly (a PWM_FREQUENCY_OVERRIDE_HZ experiment build leaves it off).
constexpr bool     SYNC_AVAILABLE    = 2 * PWM_ARR == 25 * SYNC_PERIOD_TICKS;
// Start the clock at boot, before the current-sense zero is measured: once U9 is locked its ripple lands on the
// samples as a fixed offset (board 2 on USB power: up to ~100 counts on M1b), which the zero then takes out.
// A board without the capacitor (v1.0 unmodified) just toggles an unconnected pin.  #SYNC 0 turns it off.
constexpr bool SYNC_AT_BOOT = SYNC_AVAILABLE;
// U9's ripple offset follows its input voltage (board 2: booted on USB, then 36 V moved M1b's zero by ~55 counts),
// so with the clock running the zero is measured again when the bus moves this far, with the drive off.
constexpr float SYNC_REZERO_V = 4.0f;

// ---- Pins driven as plain GPIO ----
#define PIN_BEAM_DETECT   PA5
#define PIN_BEAM_LED      PB7
#define PIN_STATUS_LED    PA15
